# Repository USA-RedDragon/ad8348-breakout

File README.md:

# AD8348 Breakout

This board is aimed to evaluate the Analog Devices AD8348 for use as an ultra-wideband SDR receiver.

## Current Status

Pre-production: I have ordered the v0.1 PCBs from OSHPark and the rest of the parts from Mouser. I will update the README when this is assembled and as testing is done.

## BOM

As of writing, the BOM comes out to $21.83 USD.

Octopart: https://octopart.com/bom-tool/jktUOUBK

## Size

1.36 x 1.33 inch (34.6 x 33.8 mm) 2 layer board.

## Images

All images below are of V0.1.

### Top Right Angled View

### Top

## Bottom

## Usage

TODO

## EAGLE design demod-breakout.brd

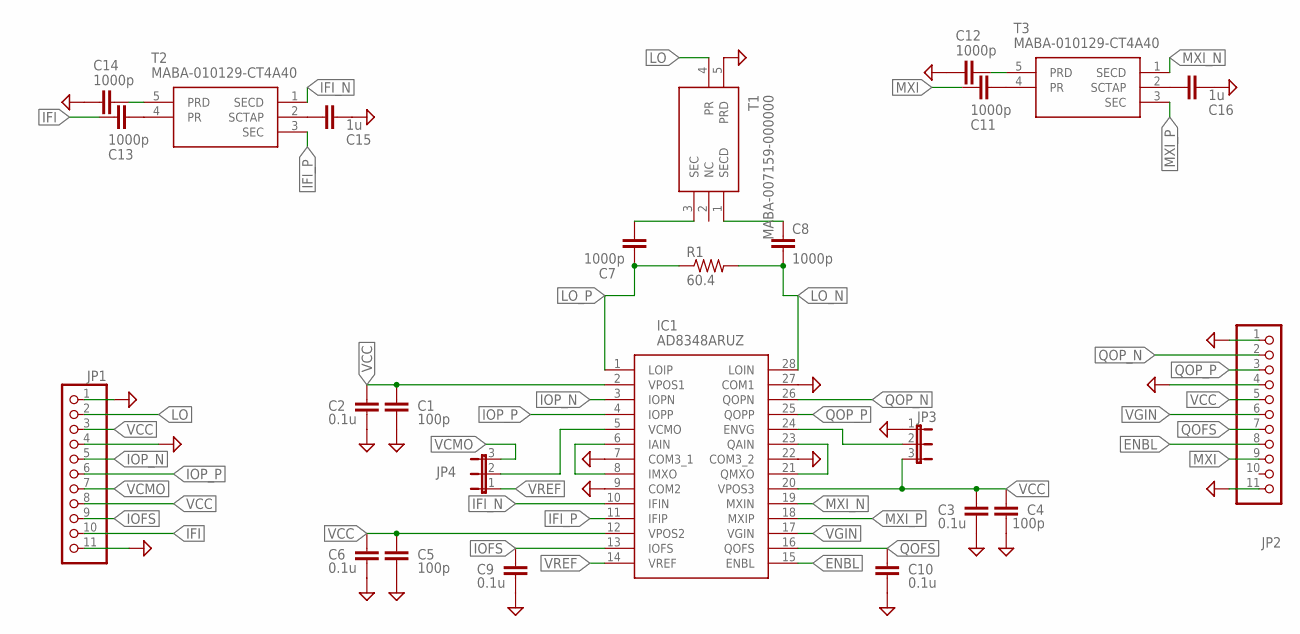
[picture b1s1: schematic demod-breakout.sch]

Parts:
C1, C4, C5: 100p; C0402
C2, C3, C6, C9, C10: 0.1u; C0402
C7, C8, C11, C12, C13, C14: 1000p; C0402
C15, C16: 1u; C0603
IC1: AD8348ARUZ; SOP65P640X120-28N
JP1, JP2: PINHD-1X11; 1X11
JP3: VGA; JP2
JP4: VCMO; JP2
R1: 60.4; R0402
T1: MABA-007159-000000; E_SERIES_1
T2, T3: MABA-010129-CT4A40; MABA010129CT4A40

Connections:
ENBL: IC1.15 (ENBL), JP2.8
ENVG: IC1.24 (ENVG), JP3.2
GND: C1.2, C2.2, C3.2, C4.2, C5.2, C6.2, C9.2, C10.2, C12.2, C14.2, C15.2, C16.2, IC1.7 (COM3_1), IC1.9 (COM2), IC1.22 (COM3_2), IC1.27 (COM1), JP1.1, JP1.4, JP1.11, JP2.1, JP2.4, JP2.11, JP3.1, T1.5 (PRD)
IFI: C13.1, JP1.10
IFI_N: IC1.10 (IFIN), T2.1 (SECD)
IFI_P: IC1.11 (IFIP), T2.3 (SEC)
IOFS: C9.1, IC1.13 (IOFS), JP1.9
IOP_N: IC1.3 (IOPN), JP1.5
IOP_P: IC1.4 (IOPP), JP1.6
LO: JP1.2, T1.4 (PR)
LO_N: C8.2, IC1.28 (LOIN), R1.2
LO_P: C7.2, IC1.1 (LOIP), R1.1
MXI: C11.1, JP2.9
MXI_N: IC1.19 (MXIN), T3.1 (SECD)
MXI_P: IC1.18 (MXIP), T3.3 (SEC)
unnamed: IC1.6 (IAIN), IC1.8 (IMXO)
unnamed: IC1.21 (QMXO), IC1.23 (QAIN)
unnamed: IC1.5 (VCMO), JP4.2
unnamed: C15.1, T2.2 (SCTAP)
unnamed: C11.2, T3.4 (PR)
unnamed: C7.1, T1.3 (SEC)
unnamed: C8.1, T1.1 (SECD)
unnamed: C13.2, T2.4 (PR)
unnamed: C14.1, T2.5 (PRD)
unnamed: C12.1, T3.5 (PRD)
unnamed: C16.1, T3.2 (SCTAP)
QOFS: C10.1, IC1.16 (QOFS), JP2.7
QOP_N: IC1.26 (QOPN), JP2.2
QOP_P: IC1.25 (QOPP), JP2.3
VCC: C1.1, C2.1, C3.1, C4.1, C5.1, C6.1, IC1.2 (VPOS1), IC1.12 (VPOS2), IC1.20 (VPOS3), JP1.3, JP1.8, JP2.5, JP3.3
VCMO: JP1.7, JP4.3
VGIN: IC1.17 (VGIN), JP2.6
VREF: IC1.14 (VREF), JP4.1

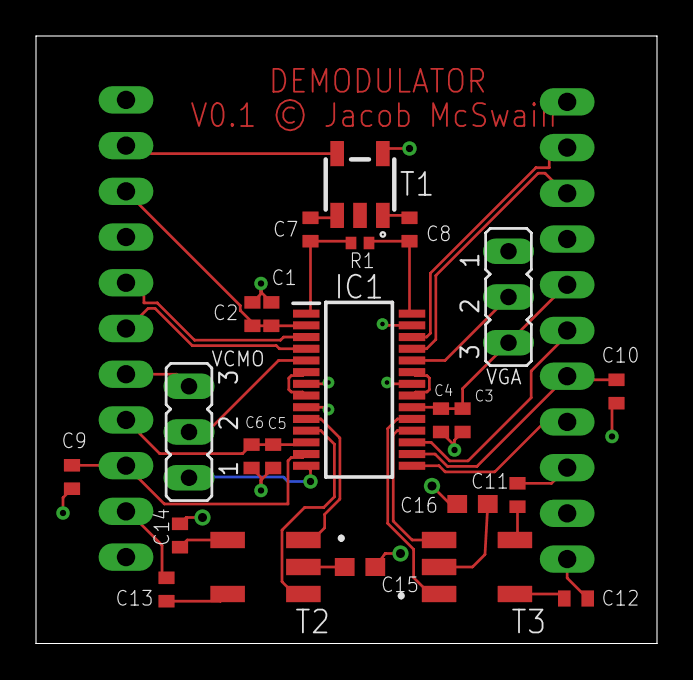
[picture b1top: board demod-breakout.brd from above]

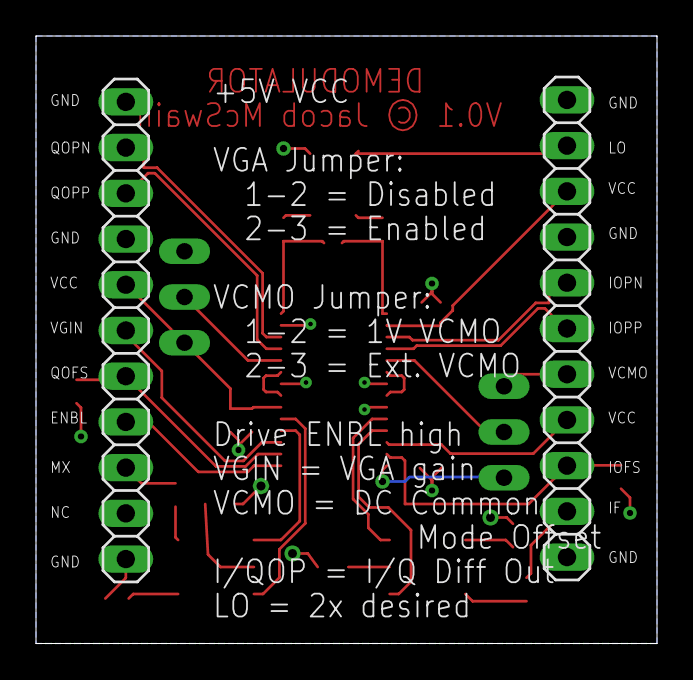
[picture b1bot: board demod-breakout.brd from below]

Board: 2 copper layers, 34.5 x 33.8 mm, 25 parts (2 on the bottom side), 33 nets.

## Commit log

2022-08-31 Revision 0.1
2022-08-31 Add MIT-0 License
2022-08-31 Add README and schematic PDF
2022-08-31 Fixup formatting of README

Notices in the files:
demod-breakout.brd:
V0.1 © Jacob McSwain
